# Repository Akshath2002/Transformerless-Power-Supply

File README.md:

# Transformerless 5V Power Supply PCB

## Overview

This project is a custom-designed transformerless AC-to-DC power supply PCB developed using **KiCad 10.0**. The circuit converts AC mains voltage into a regulated 5V DC output suitable for low-power embedded and IoT applications.

The PCB was designed from schematic capture through final layout, including component selection, footprint assignment, routing, ground plane implementation, and 3D verification.

## Features

* AC mains input
* Capacitive dropper power supply
* Full-wave bridge rectifier using 1N4007 diodes
* 7805 voltage regulation
* Input surge and filtering components
* LED power indication
* Ground plane for improved noise performance
* Through-hole component design
* Two-layer PCB layout
* Designed using KiCad 10.0

## Design Workflow

### Schematic Design

* Circuit design and simulation considerations
* Component value selection
* Power regulation stage implementation
* ERC verification

### PCB Layout

* Footprint selection
* Component placement optimization
* Power trace routing
* Ground copper pour
* DRC verification

### Mechanical Design

* Mounting holes
* Terminal block connectors
* Silkscreen labeling
* 3D model verification

## Software Used

* KiCad 10.0

## Author

**Akshath Kumar**
Electronics and Communication Engineer

## License

This project is shared for educational and learning purposes.

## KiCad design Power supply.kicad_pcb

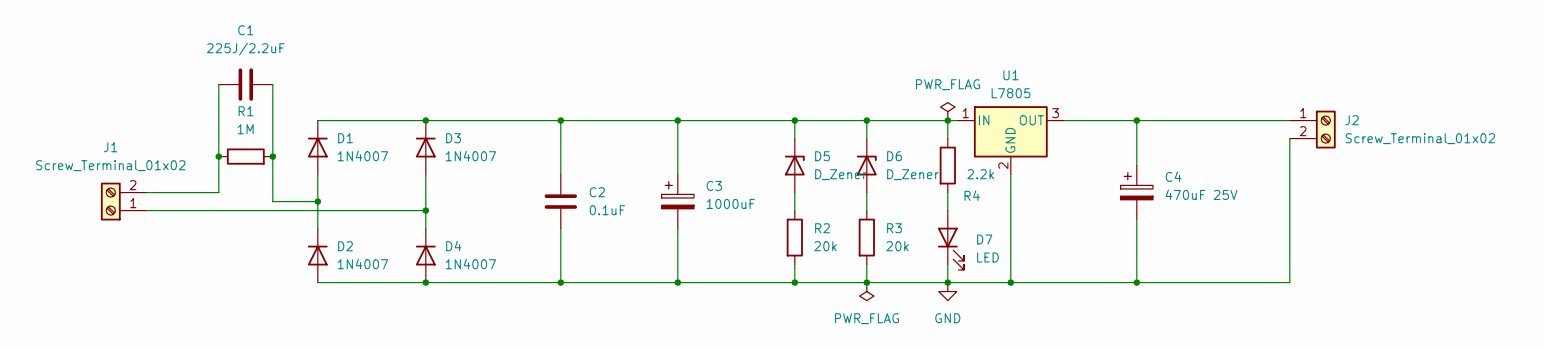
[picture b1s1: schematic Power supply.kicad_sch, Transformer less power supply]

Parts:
C1: 225J/2.2uF; C_Rect_L18.0mm_W6.0mm_P15.00mm_FKS3_FKP3
C2: 0.1uF; C_Disc_D4.7mm_W2.5mm_P5.00mm
C3: 1000uF; CP_Radial_D10.0mm_P5.00mm
C4: 470uF 25V; CP_Radial_D10.0mm_P3.80mm
D1, D2, D3, D4: 1N4007; D_DO-41_SOD81_P10.16mm_Horizontal
D5, D6: D_Zener; D_A-405_P7.62mm_Horizontal
D7: LED; LED_D5.0mm
J1, J2: Screw_Terminal_01x02; TerminalBlock_MaiXu_MX126-5.0-02P_1x02_P5.00mm
R1: 1M; R_Axial_DIN0207_L6.3mm_D2.5mm_P7.62mm_Horizontal
R2, R3: 20k; R_Axial_DIN0207_L6.3mm_D2.5mm_P7.62mm_Horizontal
R4: 2.2k; R_Axial_DIN0207_L6.3mm_D2.5mm_P7.62mm_Horizontal
U1: L7805; TO-220-3_Vertical

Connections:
GND: C2.2, C3.2, C4.2, D2.2 (A), D4.2 (A), D7.1 (K), J2.2, R2.2, R3.2, U1.2 (GND)
unnamed: C1.2, D1.2 (A), D2.1 (K), R1.2
unnamed: C2.1, C3.1, D1.1 (K), D3.1 (K), D5.1 (K), D6.1 (K), R4.1, U1.1 (IN)
unnamed: D3.2 (A), D4.1 (K), J1.1
unnamed: D5.2 (A), R2.1
unnamed: D6.2 (A), R3.1
unnamed: D7.2 (A), R4.2
unnamed: C1.1, J1.2, R1.1
unnamed: C4.1, J2.1, U1.3 (OUT)

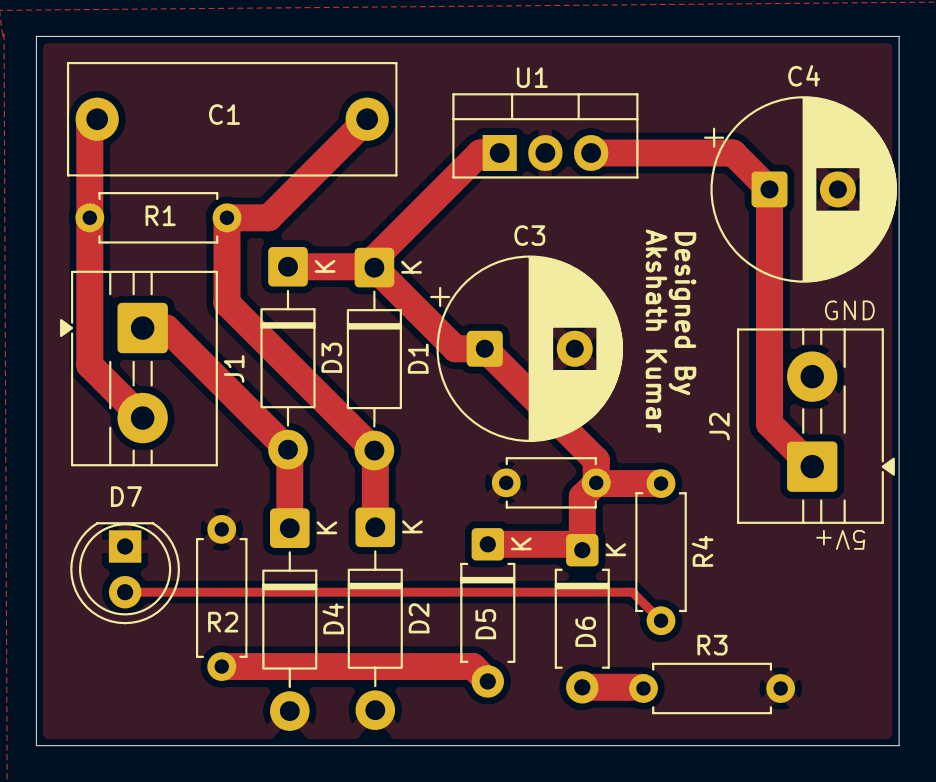
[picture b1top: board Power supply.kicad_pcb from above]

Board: 2 copper layers, 47.9 x 39.4 mm, 18 parts (0 on the bottom side), 9 nets.
